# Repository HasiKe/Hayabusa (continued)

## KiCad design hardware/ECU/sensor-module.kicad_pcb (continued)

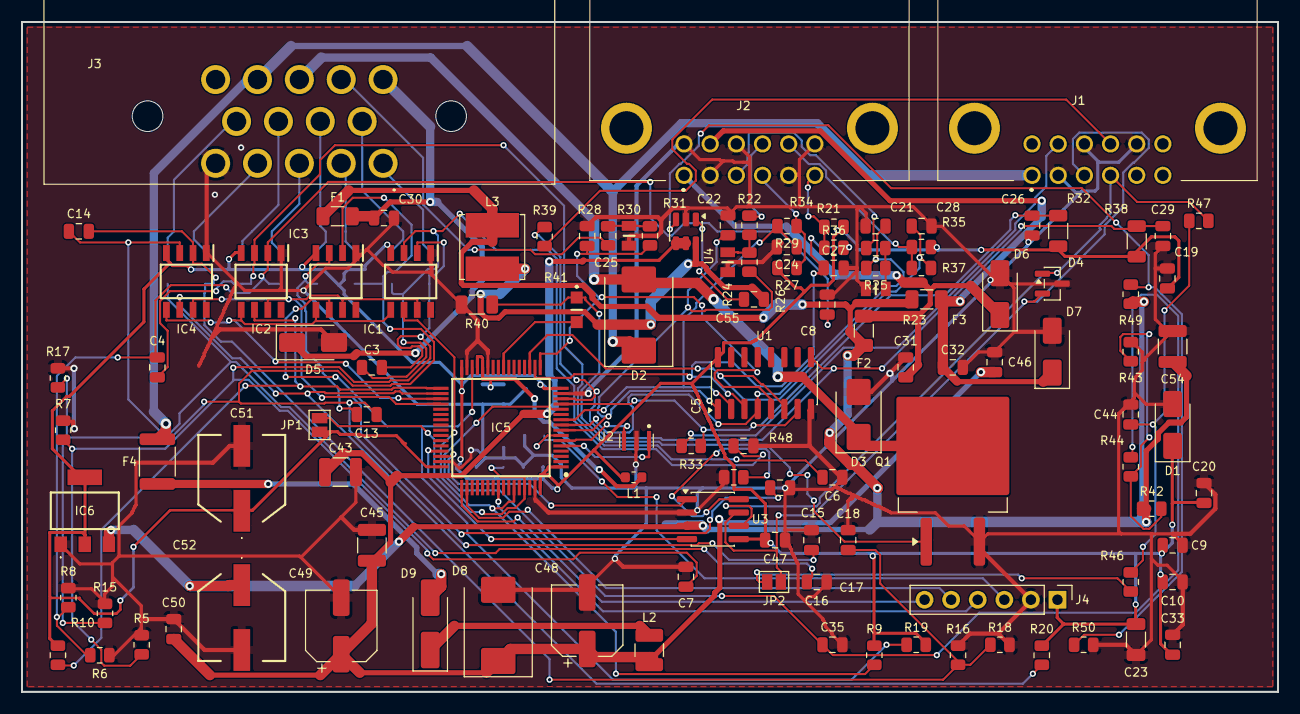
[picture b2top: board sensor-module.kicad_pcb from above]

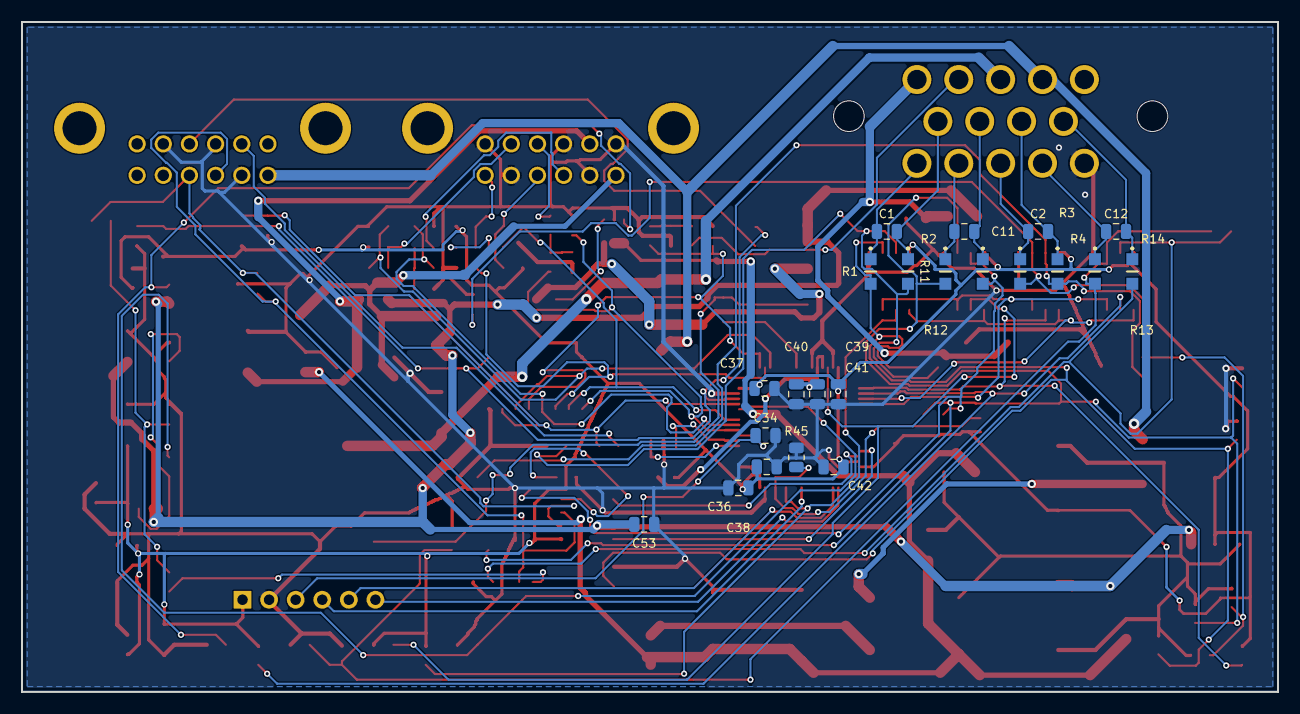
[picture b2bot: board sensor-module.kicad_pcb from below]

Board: 2 copper layers, 120.0 x 64.0 mm, 138 parts (22 on the bottom side), 74 nets.

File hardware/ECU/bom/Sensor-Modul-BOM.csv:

Reference,Qty,Value,Footprint,MPN,Manufacturer,DigiKey,DK_Stock,Mouser,MO_Stock,Chosen_Distributor,Datasheet,Validated,DNP,Notes
"C7,C5,C3,C14,C17,C18,C15,C16,C13,C4,C6,C8",12,10nF,0805,CC0805KRX7R9BB103,Yageo,311-1136-1-ND,,,,DigiKey,https://www.digikey.de/de/products/result?keywords=311-1136-1-ND,,,
"C11,C12,C1,C2",4,0.01uF,0805,CC0805KRX7R9BB103,Yageo,311-1136-1-ND,,,,DigiKey,https://www.digikey.de/de/products/result?keywords=311-1136-1-ND,,,
C23,1,100uF,1206,CL31A107MQHNNNE,Samsung Electro-Mechanics,1276-1782-1-ND,,,,DigiKey,https://www.digikey.de/de/products/result?keywords=1276-1782-1-ND,,,
C33,1,4.7uF,0805,CC0805KKX7R7BB475,Yageo,311-1883-1-ND,,,,DigiKey,https://www.digikey.de/de/products/result?keywords=311-1883-1-ND,,,
"C39,C24,C27,C28",4,1uF,0805,CC0805KKX7R7BB105,Yageo,311-1365-1-ND,,,,DigiKey,https://www.digikey.de/de/products/result?keywords=311-1365-1-ND,,,
"C43,C45",2,2.2uF/50V,1210,C3225X7R1H225K250AB,TDK,445-1431-1-ND,,,,DigiKey,https://www.digikey.de/de/products/result?keywords=445-1431-1-ND,,,
C44,1,4.7nF,0805,CC0805KRX7R9BB472,Yageo,311-1133-1-ND,,,,DigiKey,https://www.digikey.de/de/products/result?keywords=311-1133-1-ND,,,
C46,1,100nF/100V,0805,C0805C104K1RACTU,KEMET,399-C0805C104K1RACTUCT-ND,,,,DigiKey,https://www.digikey.de/de/products/result?keywords=399-C0805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,,,
"C47,C36,C37,C38,C50,C53,C41,C40,C34,C42,C26,C29",12,0.1uF,0805,CC0805KRX7R9BB104,Yageo,311-1140-1-ND,,,,DigiKey,https://www.digikey.de/de/products/result?keywords=311-1140-1-ND,,,
"C48,C49",2,33uF,CP_Elec_6.3x7.7,EEE-1HA330XP,Panasonic,PCE3925CT-ND,,,,DigiKey,https://www.digikey.de/de/products/result?keywords=PCE3925CT-ND,,,
"C51,C52",2,22 µF,EEE1AA221P,EEE-FK1H220P,Panasonic,PCE3811CT-ND,,,,DigiKey,http://industrial.panasonic.com/cdbs/www-data/pdf/RDE0000/AB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,,,Ersatz: EEE-1HA220AP war 8mm-Durchmesser (Footprint 6.3mm) + NRND
C54,1,22uF/10V,1210,GRM32ER71A226KE20L,Murata,490-1876-1-ND,,,,DigiKey,https://www.digikey.de/de/products/result?keywords=490-1876-1-ND,,,
"C55,C35,C21,C22,C25,C9,C10,C19,C20,C32,C31,C30",12,100nF,0805,CC0805KRX7R9BB104,Yageo,311-1140-1-ND,,,,DigiKey,https://www.digikey.de/de/products/result?keywords=311-1140-1-ND,,,
"D1,D7,D5,D6",4,SMAJ5.0A,SMA,SMAJ5.0A,Littelfuse,SMAJ5.0ALFCT-ND,,,,DigiKey,https://www.digikey.de/de/products/result?keywords=SMAJ5.0ALFCT-ND,,,3.3V-SMA-TVS nicht lieferbar (MCC 16 Wo.); 5V-Standoff klemmt vergleichbar
D2,1,SK510L,SMC,SK510L-TP,MCC,SK510L-TPMSCT-ND,,,,DigiKey,https://www.digikey.de/de/products/result?keywords=SK510L-TPMSCT-ND,,,Ersatz fuer SS5P10 (TO-277-Package passte nicht zu SMC-Footprint)
D3,1,SMBJ33A,SMB,SMBJ33A,Littelfuse,SMBJ33ALFCT-ND,,,,DigiKey,https://www.digikey.de/de/products/result?keywords=SMBJ33ALFCT-ND,,,
D4,1,NUP2105L,SOT-23,NUP2105LT1G,onsemi,NUP2105LT1GOSCT-ND,,,,DigiKey,https://www.digikey.de/de/products/result?keywords=NUP2105LT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,,,
D8,1,SMCJ18A,SMC,SMCJ18A,Littelfuse,SMCJ18ALFCT-ND,,,,DigiKey,https://www.digikey.de/de/products/result?keywords=SMCJ18ALFCT-ND,,,
D9,1,SL310A,SMA_Handsoldering,SL310A-TP,MCC,SL310A-TPMSCT-ND,,,,DigiKey,https://www.digikey.de/de/products/result?keywords=SL310A-TPMSCT-ND,,,
"F3,F2,F1",3,50mA,1206,0ZCJ0005FF2E,Bel Fuse,5923-0ZCJ0005FF2ECT-ND,,,,DigiKey,https://www.digikey.de/de/products/result?keywords=5923-0ZCJ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,,,
F4,1,0.5A/30V,1812,1812L050/60MR,Littelfuse,F8132CT-ND,,,,DigiKey,https://www.digikey.de/de/products/result?keywords=F8132CT-ND,,,
"IC1,IC4,IC2,IC3",4,MAX31855KASA+,SOIC127P600X175-8N,MAX31855KASA+T,Analog Devices,MAX31855KASA+TCT-ND,,700-MAX31855KASA+,,DigiKey,https://datasheets.maximintegrated.com/en/ds/MAX31855.pdf,,,
IC5,1,STM32G474RBT6,QFP50P1200X1200X160-64N,STM32G474RBT6,STMicroelectronics,STM32G474RBT6-ND,,511-STM32G474RBT6,,DigiKey,https://www.st.com/resource/en/datasheet/stm32g474cb.pdf,,,Aktuell 0 Lager bei DigiKey - Beschaffung pruefen (Alternative STM32G474RET6 pinkompatibel)
IC6,1,LD1117S33C,LD1117S33C,LD1117S33CTR,STMicroelectronics,497-1241-1-ND,,N/A,,DigiKey,https://www.st.com/resource/en/datasheet/ld1117.pdf,,,
"J2,J1",2,MX23A12NF1,MX23A12NF1,MX23A12NF1,JAE Electronics,670-1683-ND,,656-MX23A12NF1,,DigiKey,https://www.jae.com/direct/topics/topics_file_download/topic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,,,Gegenstecker MX23A12SF1 + Kontakte separat
J3,1,1-776266-1,17762661,1-776266-1,TE Connectivity,A128219-ND,,571-1-776266-1,,DigiKey,https://componentsearchengine.com/Datasheets/1/1-776266-1.pdf,,,AMPSEAL 14-pol; Gegenstecker+Kontakte separat beschaffen
J4,1,Conn_01x06_Pin,PinHeader_1x06_P2.54mm_Vertical,61300611121,Würth Elektronik,732-5319-ND,,,,DigiKey,https://www.digikey.de/de/products/result?keywords=732-5319-ND,,,
L1,1,BLM18AG601SN1,0603,BLM18AG601SN1D,Murata,490-1014-1-ND,,,,DigiKey,https://www.digikey.de/de/products/result?keywords=490-1014-1-ND,,,
L2,1,10uH/1A,1210,LQH32PN100MNCL,Murata,490-LQH32PN100MNCLCT-ND,,,,DigiKey,https://www.digikey.de/de/products/result?keywords=490-LQH32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,,,Irms 900mA / Isat 1A
L3,1,10uH/1.8A,Bourns_SRN6045TA,SRN6045TA-100M,Bourns,SRN6045TA-100MCT-ND,,,,DigiKey,https://www.digikey.de/de/products/result?keywords=SRN6045TA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,,,
Q1,1,SQM120N06-3M5L,TO-263-2,SQM120N06-3M5L_GE3,Vishay Siliconix,SQM120N06-3M5L_GE3CT-ND,,942-IRLB8721PBF,,DigiKey,http://uk.rs-online.com/web/p/products/7259322,,,Ersatz: IPB80N06S4L-07 discontinued (Infineon PCN 2023)
"R1,R4,R12,R14,R13,R11,R3,R2",8,100R,ERJ6ENF1000V,ERJ-6ENF1000V,Panasonic,P100CCT-ND,,,,DigiKey,http://docs-europe.electrocomponents.com/webdocs/13ba/090076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,,,
"R24,R23,R30",3,2k,RESC2012X60N,RC0805FR-072KL,Yageo,311-2.00KCRCT-ND,,603-RC0805FR-072KL,,DigiKey,http://www.yageo.com/documents/recent/PYu-RC_Group_51_RoHS_L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,,,
"R32,R38,R40",3,10k,1206,RC1206FR-7W10KL,Yageo,13-RC1206FR-7W10KLTR-ND,,,,DigiKey,https://www.digikey.de/de/products/result?keywords=13-RC1206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,,,
R41,1,100,ERJ6ENF1000V,ERJ-6ENF1000V,Panasonic,P100CCT-ND,,,,DigiKey,http://docs-europe.electrocomponents.com/webdocs/13ba/090076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,,,
"R42,R50,R7,R20,R17,R19,R8,R10,R9,R18",10,10k,0805,RC0805FR-0710KL,Yageo,311-10.0KCRCT-ND,,,,DigiKey,https://www.digikey.de/de/products/result?keywords=311-10.0KCRCT-ND,,,
R43,1,15k,0805,RC0805FR-0715KL,Yageo,311-15.0KCRCT-ND,,,,DigiKey,https://www.digikey.de/de/products/result?keywords=311-15.0KCRCT-ND,,,
"R44,R33,R37,R29,R22,R25,R36,R35,R26,R34,R31,R28,R21,R39,R27",15,1k,0805,RC0805FR-071KL,Yageo,311-1.00KCRCT-ND,,,,DigiKey,https://www.digikey.de/de/products/result?keywords=311-1.00KCRCT-ND,,,
R45,1,10k,0805,RC0805JR-0710KL,Yageo,311-10KARCT-ND,,,,DigiKey,https://www.digikey.de/de/products/result?keywords=311-10KARCT-ND,,,
"R47,R46",2,60R4,0805,RC0805FR-0760R4L,Yageo,311-60.4CRCT-ND,,,,DigiKey,https://www.digikey.de/de/products/result?keywords=311-60.4CRCT-ND,,,
"R48,R6,R15,R16,R5",5,0R,0805,RC0805JR-070RL,Yageo,311-0.0ARCT-ND,,,,DigiKey,https://www.digikey.de/de/products/result?keywords=311-0.0ARCT-ND,,,
R49,1,40k2,0805,RC0805FR-0740K2L,Yageo,311-40.2KCRCT-ND,,,,DigiKey,https://www.digikey.de/de/products/result?keywords=311-40.2KCRCT-ND,,,
U1,1,SP720,SOIC-16_3.9x9.9mm_P1.27mm,SP720ABTG,Littelfuse,F3162CT-ND,,,,DigiKey,https://m.littelfuse.com/~/media/electronics/datasheets/tvs_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,,,
U2,1,CSTNE16M0V530000R0,CSTNE16M0V530000R0,CSTNE16M0V530000R0,Murata,490-17948-1-ND,,81-CSTNE16M0V530000R,,DigiKey,https://www.murata.com/products/productdata/8801160822814/SP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,,,
U3,1,MCP2562FD-E/SN,SOIC-8_3.9x4.9mm_P1.27mm,MCP2562FD-E/SN,Microchip Technology,MCP2562FD-E/SN-ND,,,,DigiKey,http://ww1.microchip.com/downloads/en/DeviceDoc/25167A.pdf,,,
U4,1,TPS560430Y-Q1,SOT-23-6,TPS560430YQDBVRQ1,Texas Instruments,296-TPS560430YQDBVRQ1CT-ND,,,,DigiKey,https://www.digikey.de/de/products/result?keywords=296-TPS56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,,,X-Q1-Variante existiert nicht; Y=2.1MHz passt zu 10uH-Spule

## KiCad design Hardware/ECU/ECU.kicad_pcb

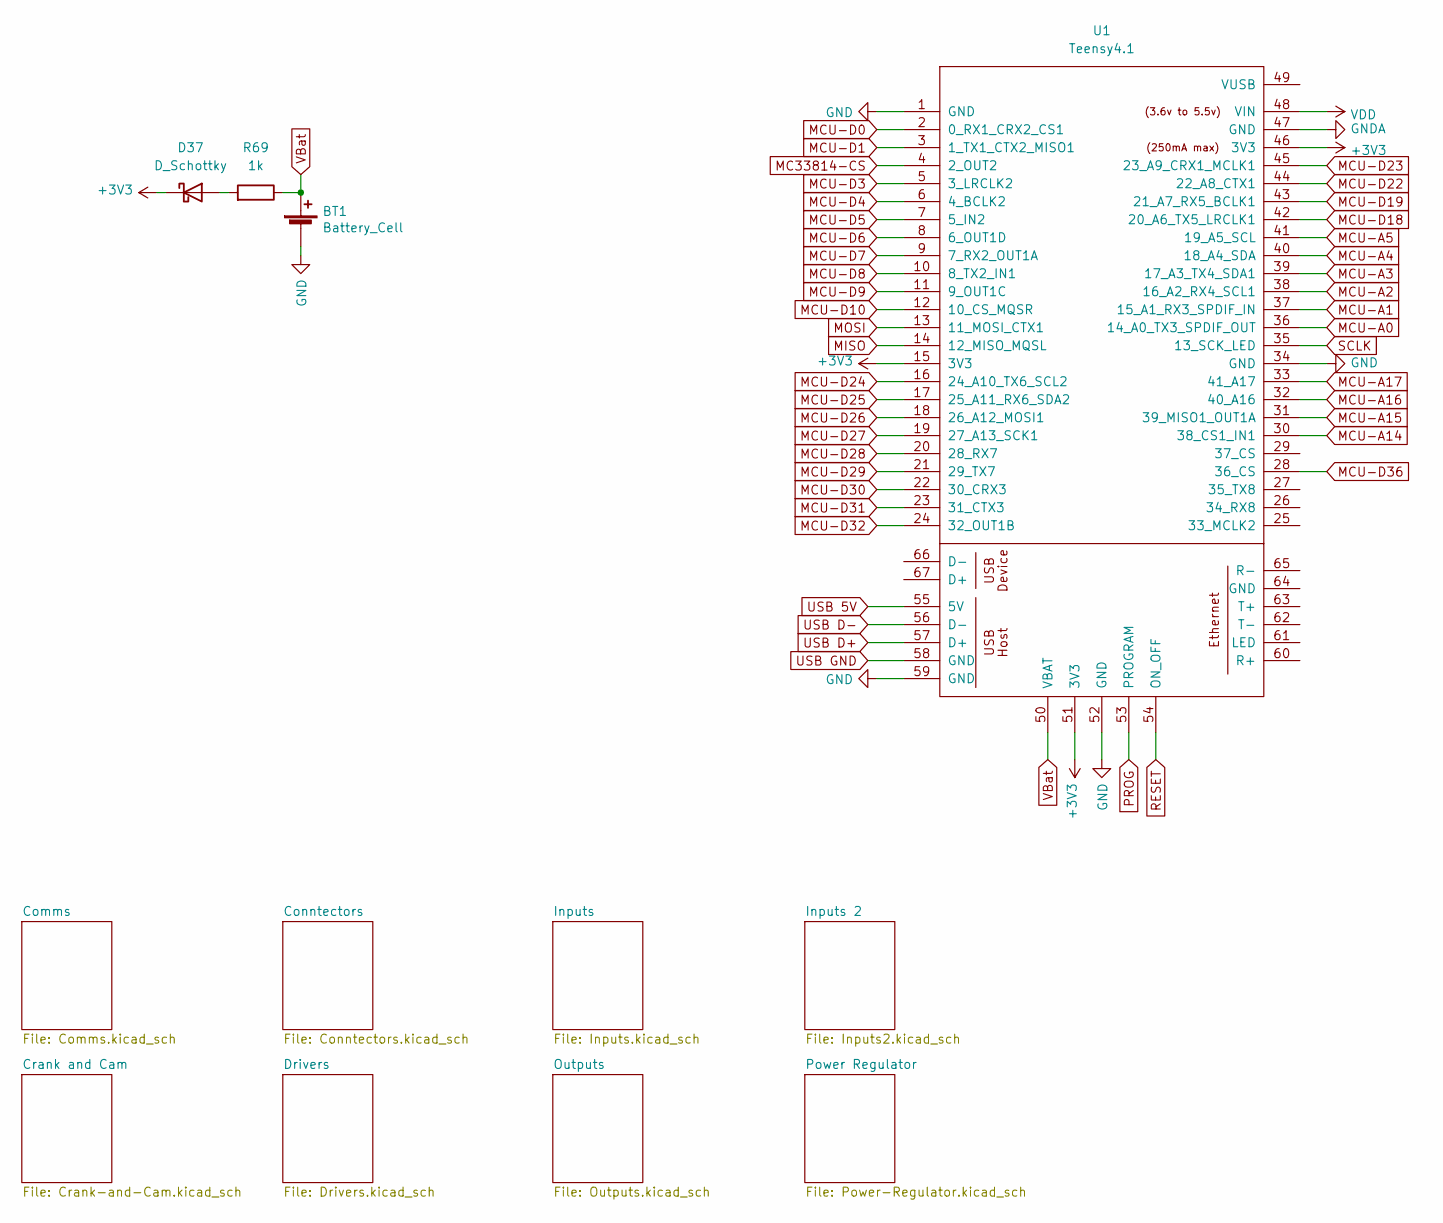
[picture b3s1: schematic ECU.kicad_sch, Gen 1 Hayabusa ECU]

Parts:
BT1: Battery_Cell; BAT_2999; Manufacturer_Part_Number 2999; Digikey Part Number 36-2999-ND
D37: D_Schottky; D_PowerDI-123
R69: 1k; R_0805_2012Metric; Manufacturer_Part_Number RC0805FR-071KL; Digikey Part Number 311-1.00KCRCT-ND
U1: Teensy4.1; Teensy41

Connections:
+3V3: D37.1 (K), U1.15 (3V3), U1.46 (3V3), U1.51 (3V3); also elsewhere on the board
+5V: U1.48 (VIN); also elsewhere on the board
ADC-Clamp-3: U1.33 (41_A17); also elsewhere on the board
ADC-Clamp-4: U1.32 (40_A16); also elsewhere on the board
ADC-Clamp-5: U1.30 (38_CS1_IN1); also elsewhere on the board
ADC-Clamp-6: U1.28 (36_CS); also elsewhere on the board
ADC-Clamp-7: U1.31 (39_MISO1_OUT1A); also elsewhere on the board
ADC-Clamp-11: U1.36 (14_A0_TX3_SPDIF_OUT); also elsewhere on the board
ADC-Clamp-12: U1.37 (15_A1_RX3_SPDIF_IN); also elsewhere on the board
ADC-Clamp-13: U1.38 (16_A2_RX4_SCL1); also elsewhere on the board
ADC-Clamp-14: U1.39 (17_A3_TX4_SDA1); also elsewhere on the board
GND: BT1.2 (-), U1.1 (GND), U1.34 (GND), U1.52 (GND), U1.59 (GND); also elsewhere on the board
GNDA: U1.47 (GND); also elsewhere on the board
MC33810_1-CS: U1.12 (10_CS_MQSR); also elsewhere on the board
MC33814-CS: U1.4 (2_OUT2); also elsewhere on the board
MCU-A4: U1.40 (18_A4_SDA); also elsewhere on the board
MCU-A5: U1.41 (19_A5_SCL); also elsewhere on the board
MCU-D0: U1.2 (0_RX1_CRX2_CS1); also elsewhere on the board
MCU-D1: U1.3 (1_TX1_CTX2_MISO1); also elsewhere on the board
MCU-D3: U1.5 (3_LRCLK2)
MCU-D4: U1.6 (4_BCLK2)
MCU-D5: U1.7 (5_IN2); also elsewhere on the board
MCU-D6: U1.8 (6_OUT1D); also elsewhere on the board
MCU-D7: U1.9 (7_RX2_OUT1A); also elsewhere on the board
MCU-D8: U1.10 (8_TX2_IN1); also elsewhere on the board
MCU-D9: U1.11 (9_OUT1C)
MCU-D18: U1.42 (20_A6_TX5_LRCLK1); also elsewhere on the board
MCU-D19: U1.43 (21_A7_RX5_BCLK1); also elsewhere on the board
MCU-D22: U1.44 (22_A8_CTX1); also elsewhere on the board
MCU-D23: U1.45 (23_A9_CRX1_MCLK1); also elsewhere on the board
MCU-D24: U1.16 (24_A10_TX6_SCL2); also elsewhere on the board
MCU-D25: U1.17 (25_A11_RX6_SDA2); also elsewhere on the board
MCU-D26: U1.18 (26_A12_MOSI1); also elsewhere on the board
MCU-D27: U1.19 (27_A13_SCK1); also elsewhere on the board
MCU-D28: U1.20 (28_RX7); also elsewhere on the board
MCU-D29: U1.21 (29_TX7); also elsewhere on the board
MCU-D30: U1.22 (30_CRX3); also elsewhere on the board
MCU-D31: U1.23 (31_CTX3); also elsewhere on the board
MCU-D32: U1.24 (32_OUT1B); also elsewhere on the board
MISO: U1.14 (12_MISO_MQSL); also elsewhere on the board
MOSI: U1.13 (11_MOSI_CTX1); also elsewhere on the board
unnamed: D37.2 (A), R69.2
PROG: U1.53 (PROGRAM)
RESET: U1.54 (ON_OFF)
SCLK: U1.35 (13_SCK_LED); also elsewhere on the board
USB 5V: U1.55 (5V); also elsewhere on the board
USB D+: U1.57 (D+); also elsewhere on the board
USB D-: U1.56 (D-); also elsewhere on the board
USB GND: U1.58 (GND); also elsewhere on the board
VBat: BT1.1 (+), R69.1, U1.50 (VBAT)

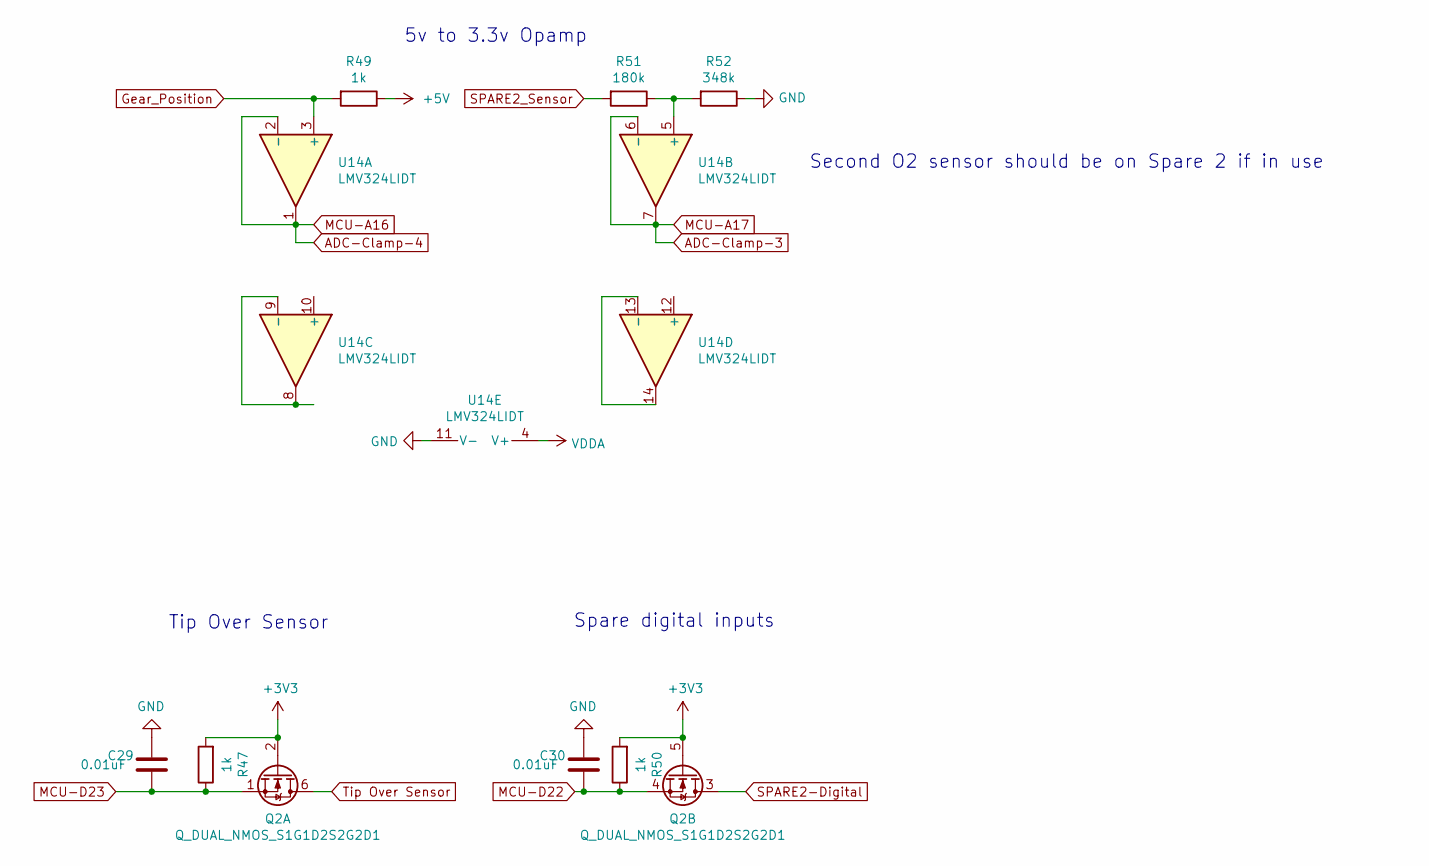
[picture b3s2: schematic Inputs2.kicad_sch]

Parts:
C29, C30: 0.01uF; C_0805_2012Metric; Manufacturer_Part_Number CC0805KRX7R9BB103; Digikey Part Number 311-1136-1-ND
Q2: Q_DUAL_NMOS_S1G1D2S2G2D1; SOT-363_SC-70-6; Manufacturer_Part_Number NVJD5121NT1G; Digikey Part Number NVJD5121NT1GOSCT-ND
R47, R50: 1k; R_0805_2012Metric; Manufacturer_Part_Number RC0805FR-071KL; Digikey Part Number 311-1.00KCRCT-ND
R49: 1k; R_0805_2012Metric; Manufacturer_Part_Number ERJ-6ENF3483V; Digikey Part Number P348KCDKR-ND
R51: 180k; R_0805_2012Metric; Manufacturer_Part_Number RC0805FR-07180KL; Digikey Part Number 311-180KCRCT-ND
R52: 348k; R_0805_2012Metric; Manufacturer_Part_Number ERJ-6ENF3483V; Digikey Part Number P348KCDKR-ND
U14: LMV324LIDT; SOIC-14_3.9x8.7mm_P1.27mm; Manufacturer_Part_Number LMV324LIDT; Digikey Part Number 497-13052-1-ND

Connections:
+3V3: Q2.2 (G), Q2.5 (G), R47.2, R50.2; also elsewhere on the board
+5V: R49.1; also elsewhere on the board
ADC-Clamp-3: U14.6 (-), U14.7; also elsewhere on the board
ADC-Clamp-4: U14.1, U14.2 (-); also elsewhere on the board
GND: C29.1, C30.1, R52.1, U14.11 (V-); also elsewhere on the board
Gear_Position: R49.2, U14.3 (+); also elsewhere on the board
MCU-D22: C30.2, Q2.4 (S), R50.1; also elsewhere on the board
MCU-D23: C29.2, Q2.1 (S), R47.1; also elsewhere on the board
unnamed: R51.1, R52.2, U14.5 (+)
unnamed: U14.8, U14.9 (-)
unnamed: U14.13 (-), U14.14
SPARE2-Digital: Q2.3 (D); also elsewhere on the board
SPARE2_Sensor: R51.2; also elsewhere on the board
Tip Over Sensor: Q2.6 (D); also elsewhere on the board
VDDA: U14.4 (V+); also elsewhere on the board

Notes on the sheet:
Spare digital inputs
Second O2 sensor should be on Spare 2 if in use
5v to 3.3v Opamp
Tip Over Sensor

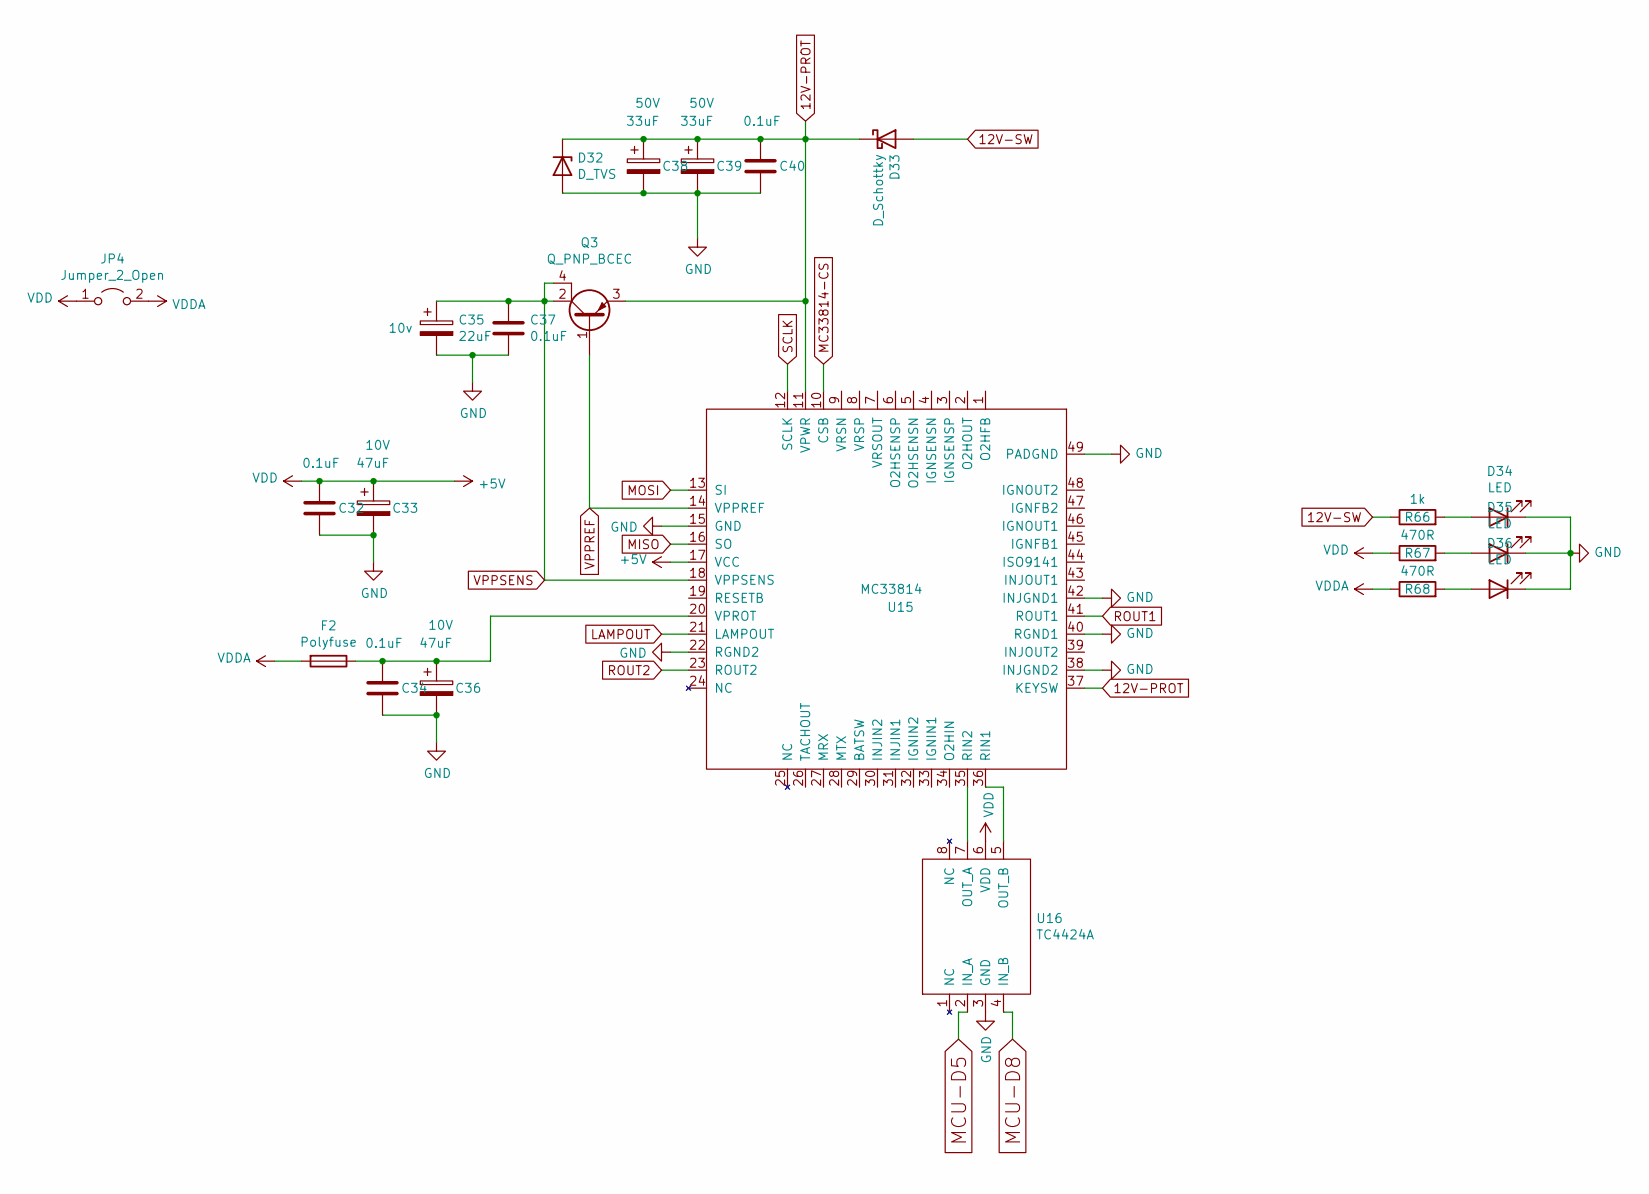
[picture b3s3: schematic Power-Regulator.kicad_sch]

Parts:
C32, C34, C37, C40: 0.1uF; C_0805_2012Metric; Manufacturer_Part_Number CC0805KRX7R9BB104; Digikey Part Number 311-1140-1-ND
C33, C36: 47uF; CP_EIA-3528-21_Kemet-B; Voltage 10V; Manufacturer_Part_Number TAJB476K006RNJ; Digikey Part Number 478-1692-1-ND
C35: 22uF; CP_Elec_4x5.4; Voltage 10v; Manufacturer_Part_Number PCE3882CT-ND; Digikey Part Number EEE-1CA220WR
C38, C39: 33uF; CP_Elec_6.3x7.7; Voltage 50V; Manufacturer_Part_Number EEE-1HA330XP; Digikey Part Number PCE3925CT-ND
D32: D_TVS; D_SMB; Manufacturer_Part_Number SMBJ40A-Q; Digikey Part Number SMBJ40A-QCT-ND
D33: D_Schottky; D_SMA_Handsoldering; Manufacturer_Part_Number B360A-13-F; Digikey Part Number B360A-FDICT-ND
D34, D35, D36: LED; LED_0805_2012Metric_Pad1.15x1.40mm_HandSolder; Manufacturer_Part_Number LG R971-KN-1; Digikey Part Number 475-1410-2-ND
F2: Polyfuse; Fuse_0603_1608Metric; Manufacturer_Part_Number 0ZCM0008FF2G; Digikey Part Number 507-1817-1-ND
JP4: Jumper_2_Open; SolderJumper-2_P1.3mm_Open_Pad1.0x1.5mm
Q3: Q_PNP_BCEC; SOT-223-3_TabPin2; Manufacturer_Part_Number FZT753TA; Digikey Part Number FZT753CT-ND
R66: 1k; R_0805_2012Metric; Manufacturer_Part_Number RC0805FR-071KL; Digikey Part Number 311-1.00KCRCT-ND
R67, R68: 470R; R_0805_2012Metric; Manufacturer_Part_Number ERJ-6ENF4700V; Digikey Part Number P470CCT-ND
U15: MC33814; LQFP-48-1EP_7x7mm_P0.5mm_EP3.6x3.6mm_ThermalVias; Manufacturer_Part_Number MC33814AE
U16: TC4424A; SOIC-8_3.9x4.9mm_P1.27mm; Manufacturer_Part_Number TC4424AVOA; Digikey Part Number TC4424AVOA-ND

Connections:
12V-PROT: C38.1, C39.1, C40.1, D32.1 (K), D33.1 (K), Q3.3 (E), U15.11 (VPWR), U15.37 (KEYSW)
12V-SW: D33.2 (A), R66.1; also elsewhere on the board
+5V: C32.1, C33.1, JP4.1 (A), R67.1, U15.17 (VCC), U16.6 (VDD); also elsewhere on the board
GND: C32.2, C33.2, C34.2, C35.2, C36.2, C37.2, C38.2, C39.2, C40.2, D32.2 (A), D34.1 (K), D35.1 (K), D36.1 (K), U15.15 (GND), U15.22 (RGND2), U15.38 (INJGND2), U15.40 (RGND1), U15.42 (INJGND1), U15.49 (PADGND), U16.3 (GND); also elsewhere on the board
LAMPOUT: U15.21 (LAMPOUT)
MC33814-CS: U15.10 (CSB); also elsewhere on the board
MCU-D5: U16.2 (IN_A); also elsewhere on the board
MCU-D8: U16.4 (IN_B); also elsewhere on the board
MISO: U15.16 (SO); also elsewhere on the board
MOSI: U15.13 (SI); also elsewhere on the board
unnamed: D34.2 (A), R66.2
unnamed: D35.2 (A), R67.2
unnamed: D36.2 (A), R68.2
unnamed: U15.36 (RIN1), U16.5 (OUT_B)
unnamed: U15.35 (RIN2), U16.7 (OUT_A)
unnamed: C34.1, C36.1, F2.1, U15.20 (VPROT)
ROUT2: U15.23 (ROUT2); also elsewhere on the board
SCLK: U15.12 (SCLK); also elsewhere on the board
VDDA: F2.2, JP4.2 (B), R68.1; also elsewhere on the board
VPPREF: Q3.1 (B), U15.14 (VPPREF)
VPPSENS: C35.1, C37.1, Q3.2 (C), Q3.4 (C), U15.18 (VPPSENS)

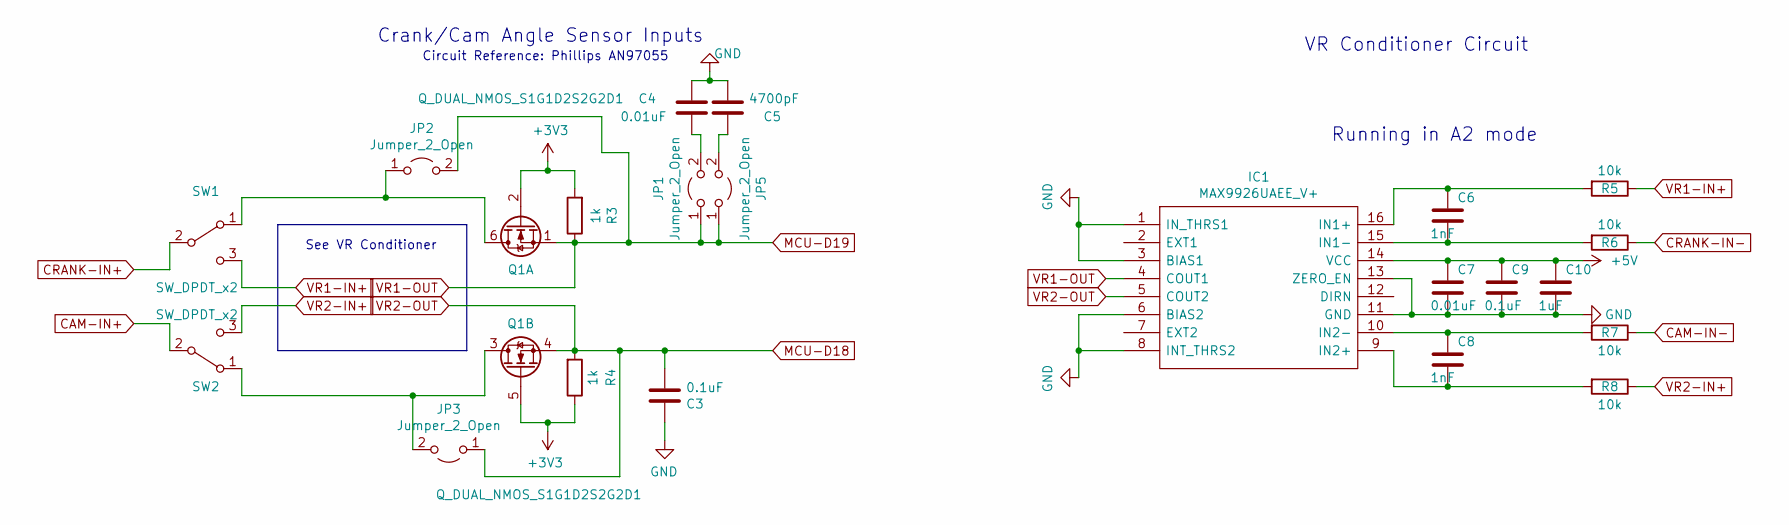
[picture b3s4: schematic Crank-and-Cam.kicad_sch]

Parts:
C3, C9: 0.1uF; C_0805_2012Metric; Manufacturer_Part_Number CC0805KRX7R9BB104; Digikey Part Number 311-1140-1-ND
C4, C7: 0.01uF; C_0805_2012Metric; Manufacturer_Part_Number CC0805KRX7R9BB103; Digikey Part Number 311-1136-1-ND
C5: 4700pF; C_0805_2012Metric; Manufacturer_Part_Number CC0805KRX7R9BB472; Digikey Part Number 311-1133-1-ND
C6, C8: 1nF; C_0805_2012Metric; Manufacturer_Part_Number C0805C102J5HACAUTO; Digikey Part Number 399-16591-1-ND
C10: 1uF; C_0805_2012Metric; Manufacturer_Part_Number CC0805KKX7R7BB105; Digikey Part Number 311-1365-1-ND
IC1: MAX9926UAEE_V+; QSOP-16_3.9x4.9mm_P0.635mm; Manufacturer_Part_Number MAX9926UAEE/V+; Mouser Part Number 700-MAX9926UAEE/V+
JP1, JP2, JP3, JP5: Jumper_2_Open; SolderJumper-2_P1.3mm_Open_Pad1.0x1.5mm
Q1: Q_DUAL_NMOS_S1G1D2S2G2D1; SOT-363_SC-70-6; Manufacturer_Part_Number NVJD5121NT1G; Digikey Part Number NVJD5121NT1GOSCT-ND
R3, R4: 1k; R_0805_2012Metric; Manufacturer_Part_Number RC0805FR-071KL; Digikey Part Number 311-1.00KCRCT-ND
R5, R6, R7, R8: 10k; R_1206_3216Metric; Manufacturer_Part_Number RC1206FR-7W10KL; Digikey Part Number 13-RC1206FR-7W10KLTR-ND
SW1, SW2: SW_DPDT_x2; AYZ0202AGRLC; Manufacturer_Part_Number AYZ0202AGRLC; Digikey Part Number 401-2013-1-ND

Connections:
+3V3: Q1.2 (G), Q1.5 (G), R3.2, R4.1; also elsewhere on the board
+5V: C7.1, C9.1, C10.1, IC1.14 (VCC); also elsewhere on the board
CAM-IN+: SW2.2 (B); also elsewhere on the board
CAM-IN-: R7.1; also elsewhere on the board
CRANK-IN+: SW1.2 (B); also elsewhere on the board
CRANK-IN-: R6.1; also elsewhere on the board
GND: C3.1, C4.1, C5.2, C7.2, C9.2, C10.2, IC1.1 (IN_THRS1), IC1.3 (BIAS1), IC1.6 (BIAS2), IC1.8 (INT_THRS2), IC1.11 (GND), IC1.13 (ZERO_EN); also elsewhere on the board
MCU-D18: C3.2, IC1.5 (COUT2), JP3.1 (A), Q1.4 (S), R4.2; also elsewhere on the board
MCU-D19: IC1.4 (COUT1), JP1.1 (A), JP2.2 (B), JP5.1 (A), Q1.1 (S), R3.1; also elsewhere on the board
unnamed: C6.1, IC1.16 (IN1+), R5.2
unnamed: C6.2, IC1.15 (IN1-), R6.2
unnamed: C8.2, IC1.9 (IN2+), R8.2
unnamed: C8.1, IC1.10 (IN2-), R7.2
unnamed: C4.2, JP1.2 (B)
unnamed: JP2.1 (A), Q1.6 (D), SW1.1 (A)
unnamed: JP3.2 (B), Q1.3 (D), SW2.1 (A)
unnamed: C5.1, JP5.2 (B)
VR1-IN+: R5.1, SW1.3 (C)
VR2-IN+: R8.1, SW2.3 (C)

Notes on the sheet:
See VR Conditioner
VR Conditioner Circuit
Crank/Cam Angle Sensor Inputs
Running in A2 mode
Circuit Reference: Phillips AN97055

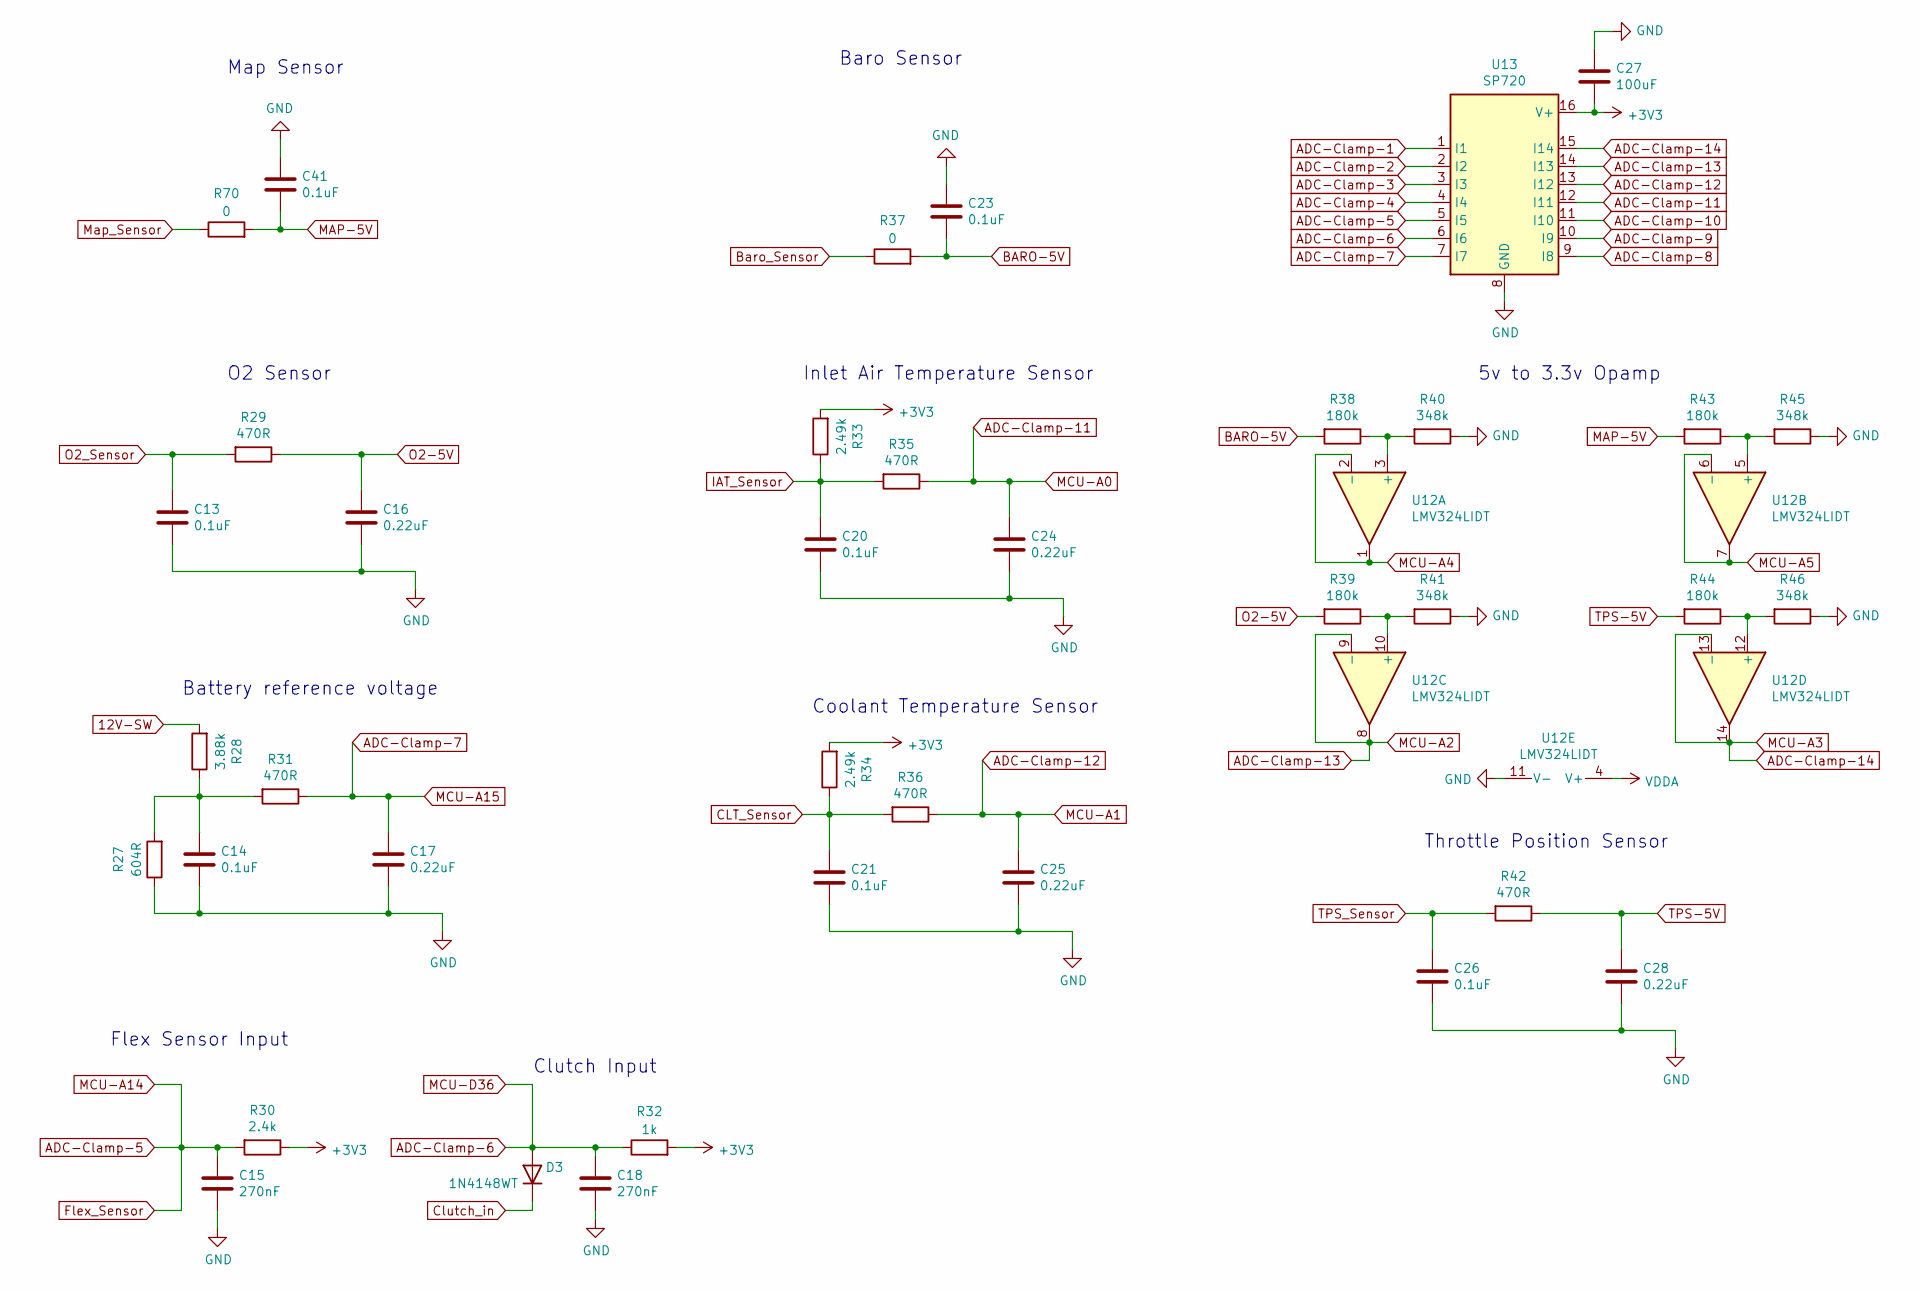
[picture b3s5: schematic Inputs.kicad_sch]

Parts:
C13, C14, C20, C21, C23, C26, C41: 0.1uF; C_0805_2012Metric; Manufacturer_Part_Number CC0805KRX7R9BB104; Digikey Part Number 311-1140-1-ND
C15, C18: 270nF; C_0805_2012Metric; Manufacturer_Part_Number CC0805JRX7R7BB274; Digikey Part Number 311-4268-1-ND
C16, C17, C24, C25, C28: 0.22uF; C_0805_2012Metric; Manufacturer_Part_Number CL21B224KOCNNNC; Digikey Part Number 1276-1284-1-ND
C27: 100uF; C_1206_3216Metric; Manufacturer_Part_Number CL31A107MQHNNNE; Digikey Part Number 1276-1782-1-ND
D3: 1N4148WT; D_SOD-523
R27: 604R; R_0805_2012Metric; Tolerance 1%; Manufacturer_Part_Number RC0805FR-07604RL; Digikey Part Number 311-604CRCT-ND
R28: 3.88k; R_0805_2012Metric_Pad1.20x1.40mm_HandSolder; Tolerance 1%; Manufacturer_Part_Number RT0603BRD073K88L; Digikey Part Number YAG4550CT-ND
R29, R31, R35, R36, R42: 470R; R_0805_2012Metric; Manufacturer_Part_Number ERJ-6ENF4700V; Digikey Part Number P470CCT-ND
R30: 2.4k; R_0805_2012Metric; Manufacturer_Part_Number RC0805FR-072K4L; Digikey Part Number 311-2.40KCRCT-ND
R32: 1k; R_0805_2012Metric; Manufacturer_Part_Number RC0805FR-071KL; Digikey Part Number 311-1.00KCRCT-ND
R33, R34: 2.49k; R_0805_2012Metric; Tolerance 0.1%; Manufacturer_Part_Number RT0805BRD072K49L; Digikey Part Number YAG1854CT-ND
R37, R70: 0; R_0805_2012Metric; Manufacturer_Part_Number ERJ-6GEY0R00V; Digikey Part Number P0.0ACT-ND
R38, R39, R43, R44: 180k; R_0805_2012Metric; Manufacturer_Part_Number RC0805FR-07180KL; Digikey Part Number 311-180KCRCT-ND
R40, R41, R45, R46: 348k; R_0805_2012Metric; Manufacturer_Part_Number ERJ-6ENF3483V; Digikey Part Number P348KCDKR-ND
U12: LMV324LIDT; SOIC-14_3.9x8.7mm_P1.27mm; Manufacturer_Part_Number LMV324LIDT; Digikey Part Number 497-13052-1-ND
U13: SP720; SOIC-16_3.9x9.9mm_P1.27mm; Manufacturer_Part_Number SP720ABTG; Digikey Part Number F3162CT-ND

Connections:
12V-SW: R28.2; also elsewhere on the board
+3V3: C27.2, R30.1, R32.2, R33.2, R34.2, U13.16 (V+); also elsewhere on the board
ADC-Clamp-1: U13.1 (I1)
ADC-Clamp-2: U13.2 (I2)
ADC-Clamp-3: U13.3 (I3); also elsewhere on the board
ADC-Clamp-4: U13.4 (I4); also elsewhere on the board
ADC-Clamp-5: C15.1, R30.2, U13.5 (I5); also elsewhere on the board
ADC-Clamp-6: C18.1, D3.2 (A), R32.1, U13.6 (I6); also elsewhere on the board
ADC-Clamp-7: C17.1, R31.1, U13.7 (I7); also elsewhere on the board
ADC-Clamp-8: U13.9 (I8)
ADC-Clamp-9: U13.10 (I9)
ADC-Clamp-10: U13.11 (I10)
ADC-Clamp-11: C24.1, R35.1, U13.12 (I11); also elsewhere on the board
ADC-Clamp-12: C25.1, R36.1, U13.13 (I12); also elsewhere on the board
ADC-Clamp-13: U12.8, U12.9 (-), U13.14 (I13); also elsewhere on the board
ADC-Clamp-14: U12.13 (-), U12.14, U13.15 (I14); also elsewhere on the board
BARO-5V: C23.2, R37.2, R38.2
Baro_Sensor: R37.1; also elsewhere on the board
CLT_Sensor: C21.1, R34.1, R36.2; also elsewhere on the board
Clutch_in: D3.1 (K); also elsewhere on the board
GND: C13.2, C14.2, C15.2, C16.2, C17.2, C18.2, C20.2, C21.2, C23.1, C24.2, C25.2, C26.2, C27.1, C28.2, C41.1, R27.1, R40.1, R41.1, R45.1, R46.1, U12.11 (V-), U13.8 (GND); also elsewhere on the board
IAT_Sensor: C20.1, R33.1, R35.2; also elsewhere on the board
MAP-5V: C41.2, R43.2, R70.2
MCU-A4: U12.1, U12.2 (-); also elsewhere on the board
MCU-A5: U12.6 (-), U12.7; also elsewhere on the board
Map_Sensor: R70.1; also elsewhere on the board
unnamed: C14.1, R27.2, R28.1, R31.2
unnamed: R38.1, R40.2, U12.3 (+)
unnamed: R43.1, R45.2, U12.5 (+)
unnamed: R39.1, R41.2, U12.10 (+)
unnamed: R44.1, R46.2, U12.12 (+)
O2-5V: C16.1, R29.1, R39.2
O2_Sensor: C13.1, R29.2; also elsewhere on the board
TPS-5V: C28.1, R42.1, R44.2
TPS_Sensor: C26.1, R42.2; also elsewhere on the board
VDDA: U12.4 (V+); also elsewhere on the board

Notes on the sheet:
Baro Sensor
Battery reference voltage
Coolant Temperature Sensor
Clutch Input
Inlet Air Temperature Sensor
Flex Sensor Input
Map Sensor
O2 Sensor
5v to 3.3v Opamp
Throttle Position Sensor
